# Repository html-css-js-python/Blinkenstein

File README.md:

# Blinkenstein

Blinkenstein is a simple KiCad PCB design intended as a functional test board.
It is designed to verify PCB manufacturing quality, assembly correctness, and basic
circuit functionality using classic CMOS logic.

## 1. Overview

Blinkenstein is an LED sequencing circuit built primarily from through-hole components,
with one SMD component included to verify mixed-technology assembly.
The design emphasizes simplicity, low power consumption, and ease of visual inspection.

## 2. Functional Description

The circuit sequentially activates LED pairs in the following order:

`RED → GREEN → BLUE → YELLOW`

Although eight LEDs are present on the PCB, only two LEDs are active at any given time.
The circuit serves as a functional indicator rather than a lighting device.

The core of the design is a CD4017 decade counter.
Clock pulses are generated by a discrete oscillator based on the tunneling effect.
These pulses are inverted and conditioned by a NOT gate with a Schmitt trigger input,
providing a clean and stable clock signal for the counter.

## 3. Schematic Diagram

Figure 1. Blinkenstein schematic diagram

## 4. Electrical Characteristics

### 4.1 Recommended Operating Conditions

| Parameter            | Symbol | Min | Typ | Max | Unit |
|----------------------|--------|-----|-----|-----|------|
| Supply Voltage       | VCC    | 7   | 9   | 12  | V    |
| Supply Current       | ICC    | -   | 100 | TBD | mA   |
| Ambient Temperature  | TA     | -20 | 25  | 60  | °C   |

### 4.2 Power Consumption

| Operating Mode   | Supply Voltage | Current | Notes            |
|------------------|----------------|---------|------------------|
| Normal operation | 9 V            | ~100 mA | Two LEDs active  |

## 5. Power Supply Requirements

- DC input voltage range: 7–12 V
- Recommended supply voltage: 9 V
- Typical current consumption: ~100 mA
- External regulation not required

## 6. PCB and Assembly Notes

- Majority of components: through-hole
- One component: SMD (for mixed-technology assembly testing)
- Suitable for hand soldering and reflow (SMD component)

## 7. Intended Applications

- PCB manufacturing test board
- Assembly verification (THT + SMD)
- Educational demonstrations (CMOS counters and oscillators)
- Visual functional indicator

## 8. Project Files

All project files (schematic, PCB layout, Gerber)
are located in the following directory:

**[Project Files](/konstantynopolitanczykowianeczka_zamieszkujaca_konstantynopol)**

## 9. Notes

This project is not intended for high-power or precision timing applications.
Component values may be adjusted without affecting core functionality.
Original project name (may appear on schematics and PCB): `Migacz`

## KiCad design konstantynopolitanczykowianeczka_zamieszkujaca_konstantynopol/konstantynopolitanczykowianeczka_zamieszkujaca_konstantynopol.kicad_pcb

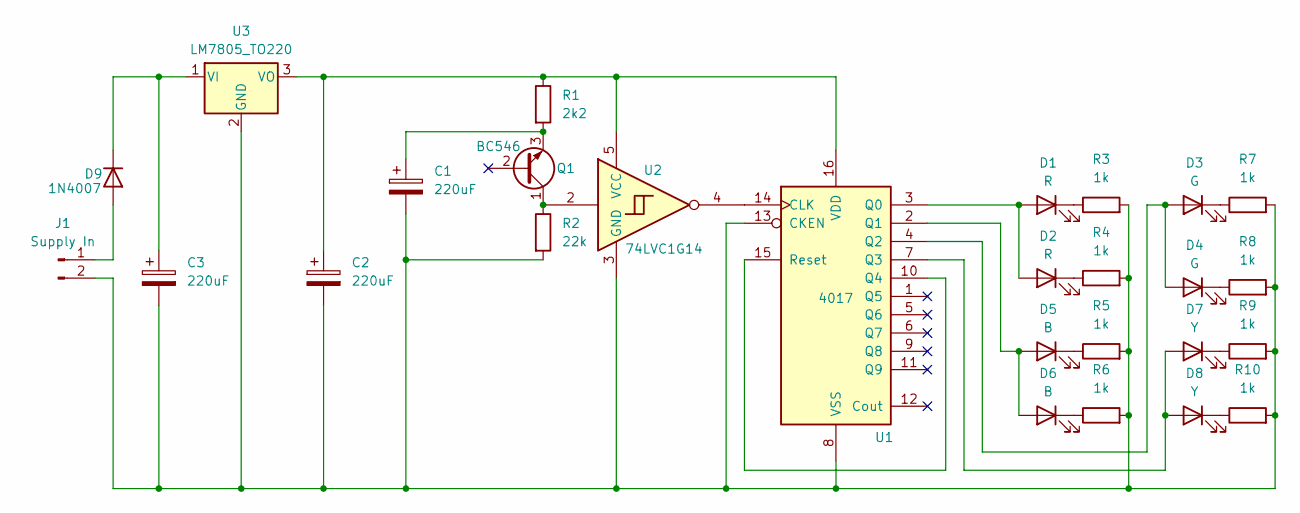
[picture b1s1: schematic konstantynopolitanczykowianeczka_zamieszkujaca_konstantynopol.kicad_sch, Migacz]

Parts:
C1, C2, C3: 220uF; CP_Radial_D8.0mm_P3.50mm
D1, D2: R; LED_D5.0mm
D3, D4: G; LED_D5.0mm
D5, D6: B; LED_D5.0mm
D7, D8: Y; LED_D5.0mm
D9: 1N4007; D_DO-41_SOD81_P10.16mm_Horizontal
J1: Supply In; PinHeader_1x02_P1.27mm_Horizontal
Q1: BC546; TO-92L_Inline
R1: 2k2; R_Axial_DIN0204_L3.6mm_D1.6mm_P7.62mm_Horizontal
R2: 22k; R_Axial_DIN0204_L3.6mm_D1.6mm_P7.62mm_Horizontal
R3, R4, R5, R6, R7, R8, R9, R10: 1k; R_Axial_DIN0204_L3.6mm_D1.6mm_P7.62mm_Horizontal
U1: 4017; DIP-16_W7.62mm_LongPads
U2: 74LVC1G14; SOT-23-5_HandSoldering
U3: LM7805_TO220; TO-220-3_Horizontal_TabDown

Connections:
unnamed: D1.2 (A), D2.2 (A), U1.3 (Q0)
unnamed: D1.1 (K), R3.1
unnamed: D2.1 (K), R4.1
unnamed: D3.2 (A), D4.2 (A), U1.4 (Q2)
unnamed: D3.1 (K), R7.1
unnamed: D4.1 (K), R8.1
unnamed: D5.2 (A), D6.2 (A), U1.2 (Q1)
unnamed: D5.1 (K), R5.1
unnamed: D6.1 (K), R6.1
unnamed: D7.2 (A), D8.2 (A), U1.7 (Q3)
unnamed: D7.1 (K), R9.1
unnamed: D8.1 (K), R10.1
unnamed: D9.2 (A), J1.1
unnamed: C3.1, D9.1 (K), U3.1 (VI)
unnamed: C1.2, C2.2, C3.2, J1.2, R2.2, R3.2, R4.2, R5.2, R6.2, R7.2, R8.2, R9.2, R10.2, U1.8 (VSS), U1.13 (CKEN), U2.3 (GND), U3.2 (GND)
unnamed: Q1.1 (C), R2.1, U2.2
unnamed: C1.1, Q1.3 (E), R1.2
unnamed: U1.14 (CLK), U2.4
unnamed: U1.10 (Q4), U1.15 (Reset)
unnamed: C2.1, R1.1, U1.16 (VDD), U2.5 (VCC), U3.3 (VO)

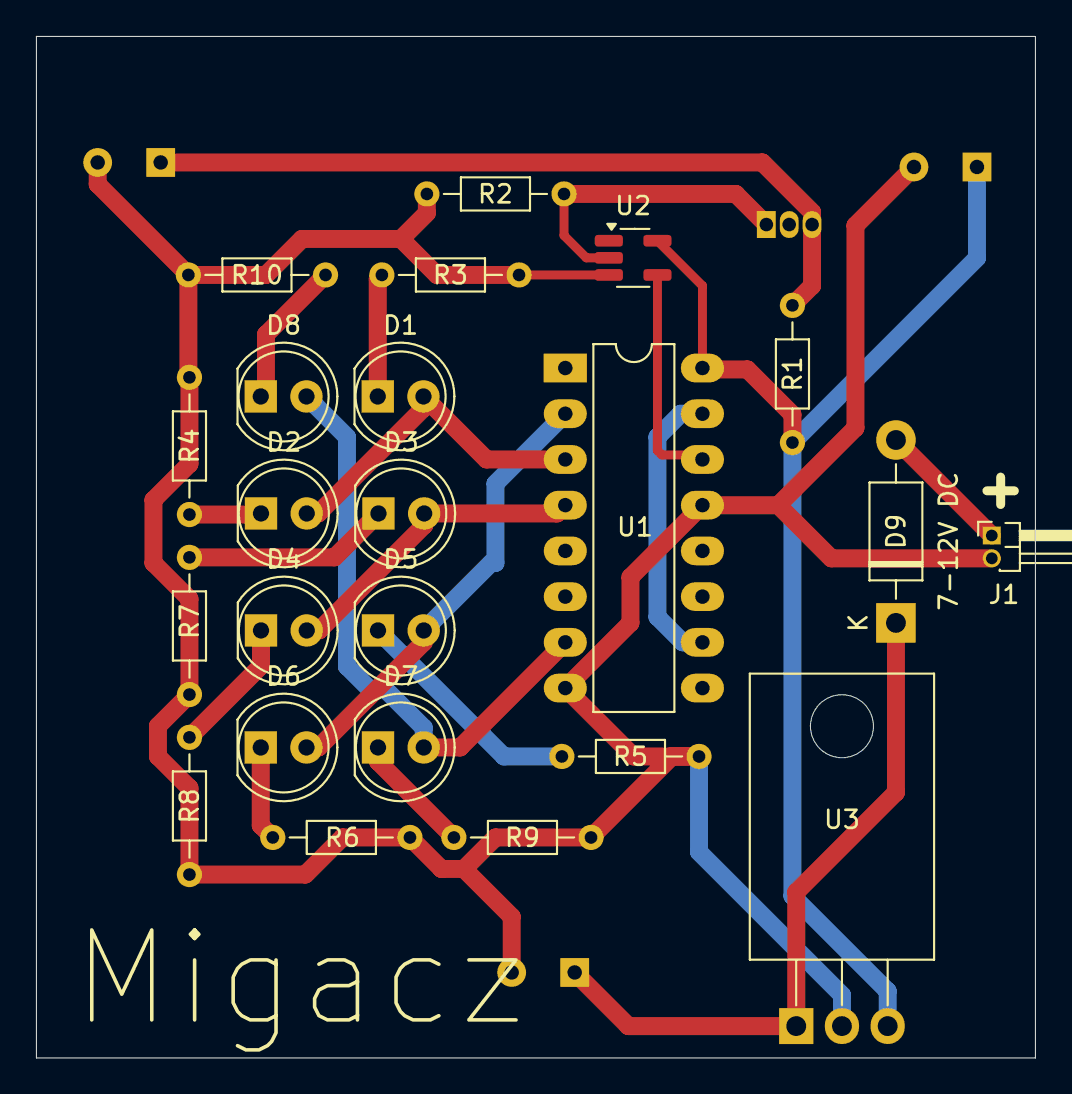
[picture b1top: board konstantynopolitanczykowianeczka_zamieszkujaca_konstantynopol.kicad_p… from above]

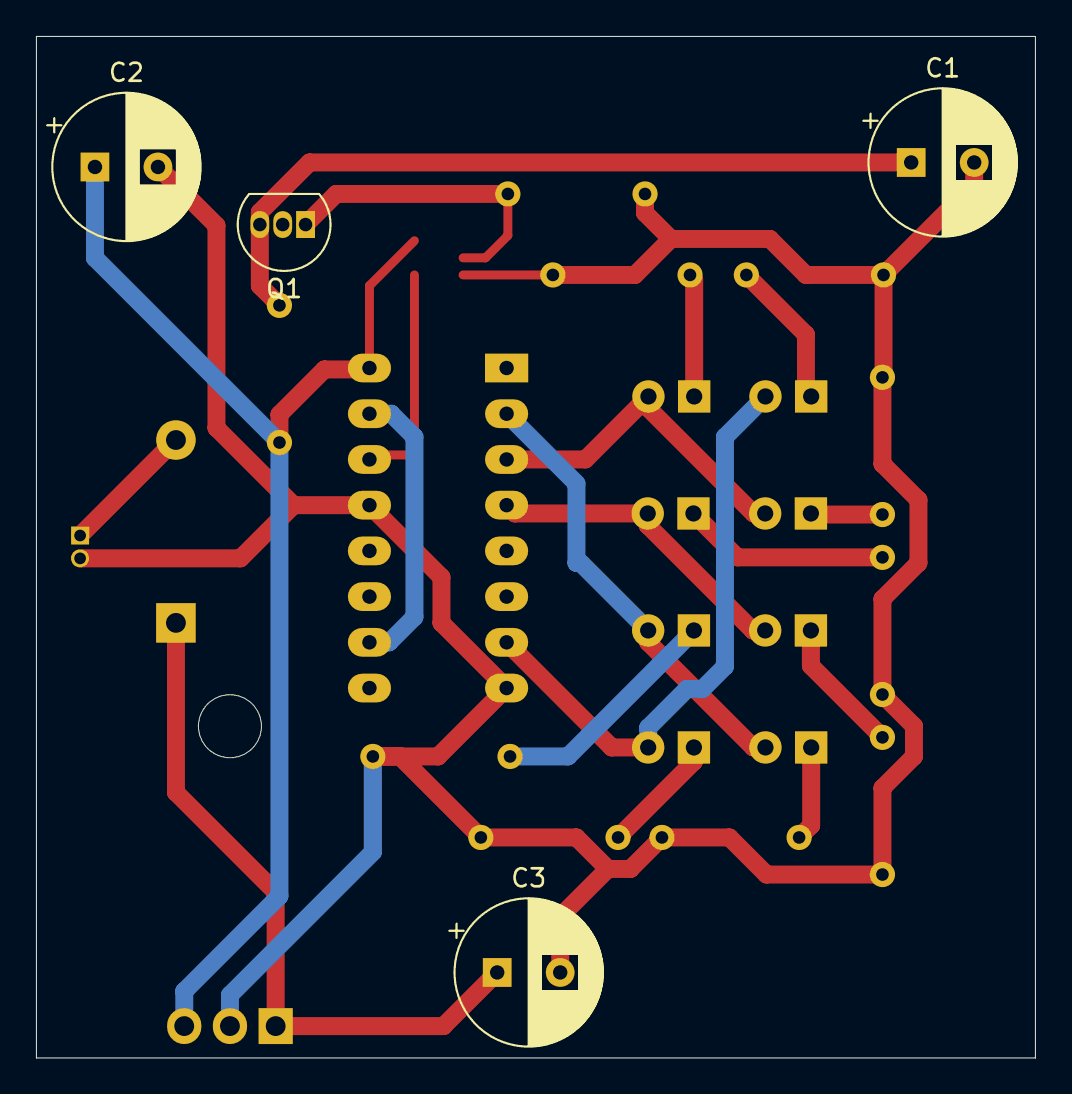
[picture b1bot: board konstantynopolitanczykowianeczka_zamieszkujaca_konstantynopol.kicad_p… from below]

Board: 2 copper layers, 55.5 x 56.8 mm, 27 parts (4 on the bottom side), 20 nets.

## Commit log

2026-02-07 Upgrade README.md
